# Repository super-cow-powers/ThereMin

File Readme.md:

# ThereMin()
Minimal Digital Theremin, based on a pair of NE555p timers and an STM32G0.

## Theory of Operation
The device uses a pair of 555 timers to translate hand-position to frequency, which is measured by the STM32 and then used to modify a generated sine wave.

The 555 timers operate in the usual astable mode except with the capacitor replaced with an "antenna"; this forms a capacitor between you and the metal whose value varies with the gap between you and the antenna, which then varies the frequency of the 555 output.

The STM32 measures the period of the 555's output wave, calculating the offset from the initial state (calibration is done at power-on); the offset from the calibrated value is used to calculate an amplitude coefficient and a pitch offset. The amplitude coefficient divides a full-scale sine wave which is stored in a lookup table. The pitch offset is used to increase or decrease the time between changes of output value (by adjusting a timer's reload-point), thus stretching or compacting the output wave as required - although with an apparently exponential response, which is partially corrected by the firmware.

The signal is fed into a TDA2822 amplifier in single-ended mode (SE gave better stability on veroboard) with the input amplitude controlled by a potentiometer; the amplifier feeds into either an (optional) internal speaker or headphone jack depending on a SPDT switch.

## Hardware
The hardware is designed in KiCad. If you want to build your own, you're free to use the files so long as you don't try and blame me for anything which goes wrong as a result; it'd be nice to keep my name on the board, too.

The devices are fairly cheap - about £12-15 for the basic device with no LEDs or pitch-adjust potentiometer (which haven't been written in) - I used JLC for the boards and sourced most of the parts from DigiKey.

The cases are drilled by hand, using a 13mm bit for the rear cables, a 6.5mm and 7.5mm bit for the front switch and pot, and a 6mm bit for the (four) holes on the top. There's no drilling template, just use a centre-punch in the right place for the hole's purpose and drill. 

### "Antennae"
The Antennae (capacitor plates, really) are not too critical. Mine are made from thin brass rod which will fit into the jacks; any conductor which fits the jacks will work - make it into a loop which looks like a theremin antenna aught, with one "leg" slightly shorter than the other for the non-connected end. The bigger the antenna the more sensitive the response generally speaking, although I've found that there's not much to gain with this device from a huge antenna.

## Firmware
The firmware uses device files from ST Micro and ARM CMSIS, the rest can be blamed on me. The ST HAL is not being used, because it looked like a good idea to not use it when I started...

The software is fairly simple although does make heavy use of the DMA engine and Timers - these are described in the chip reference manual and, briefly, in comments.

### Building
The firmware builds with Make and Arm GCC (I suspect ARMCC6 would work, too, but I'm not going to try it) and should build on most *nix systems - it might work on Windows under WSL or mingw, but you're on your own with that one. For anyone who doesn't want to build the firmware, the latest binary is just in the build directory.

The firmware can be flashed with your favourite flashing tool; a script for an ST-Link V2 with OpenOCD is provided, but I recommend just using STMCubeProg if you're either inexperienced or running Windows. 

-----

This was initially designed as a lab kit for the [York Engineering Society](https://github.com/EngYork).

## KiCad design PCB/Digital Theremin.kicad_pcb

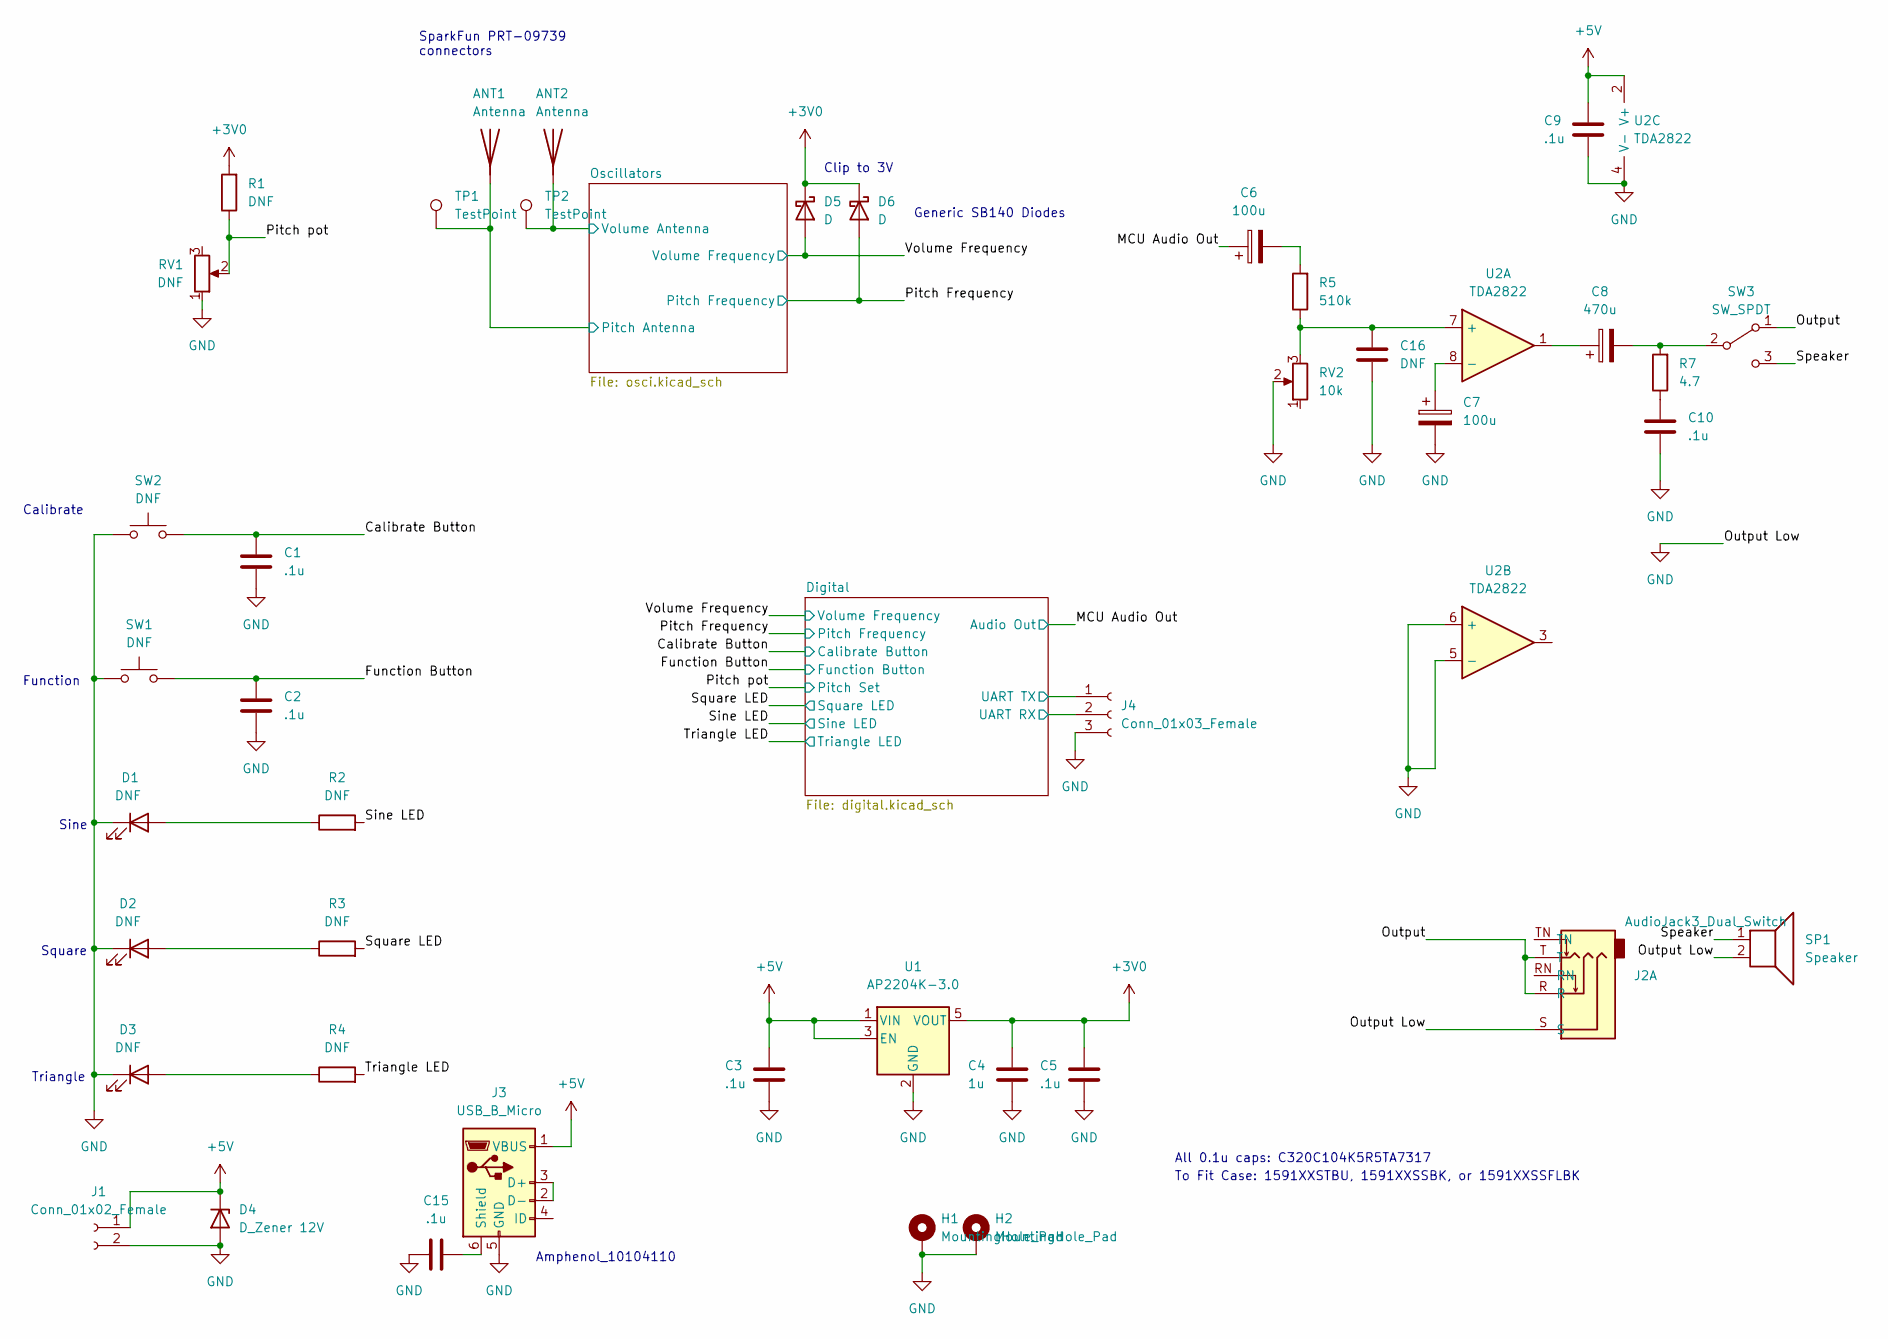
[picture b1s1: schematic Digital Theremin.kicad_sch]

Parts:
ANT1, ANT2: Antenna; MountingHole_3.2mm_M3_Pad_Via
C1, C2, C3, C5, C9, C10, C15: .1u; C_Rect_L4.0mm_W2.5mm_P2.50mm
C4: 1u; C_Rect_L4.0mm_W2.5mm_P2.50mm
C6, C7: 100u; CP_Radial_D5.0mm_P2.50mm
C8: 470u; CP_Radial_D5.0mm_P2.50mm
C16: DNF; C_Rect_L4.0mm_W2.5mm_P2.50mm
D1, D2, D3: DNF; LED_D5.0mm
D4: D_Zener 12V; D_DO-41_SOD81_P10.16mm_Horizontal
D5, D6: D; D_DO-41_SOD81_P10.16mm_Horizontal
H1, H2: MountingHole_Pad; MountingHole_3.7mm_Pad
J1: Conn_01x02_Female; PinHeader_1x02_P2.54mm_Vertical
J2: AudioJack3_Dual_Switch; Jack_3.5mm_CUI_SJ1-3525N_Horizontal
J3: USB_B_Micro; USB_Micro-B_Amphenol_10104110_Horizontal
J4: Conn_01x03_Female; PinHeader_1x03_P2.54mm_Vertical
R1, R2, R3, R4: DNF; R_Axial_DIN0207_L6.3mm_D2.5mm_P10.16mm_Horizontal
R5: 510k; R_Axial_DIN0207_L6.3mm_D2.5mm_P10.16mm_Horizontal
R7: 4.7; R_Axial_DIN0207_L6.3mm_D2.5mm_P10.16mm_Horizontal
RV1: DNF; PinHeader_1x03_P2.54mm_Vertical
RV2: 10k; PinHeader_1x03_P2.54mm_Vertical
SP1: Speaker; PinHeader_1x02_P2.54mm_Vertical
SW1, SW2: DNF; SW_PUSH_6mm
SW3: SW_SPDT; PinHeader_1x03_P2.54mm_Vertical
TP1, TP2: TestPoint; TestPoint_Loop_D2.50mm_Drill1.0mm
U1: AP2204K-3.0; SOT-23-5
U2: TDA2822; SOIC-8_3.9x4.9mm_P1.27mm

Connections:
+3V0: C4.1, C5.1, D5.1 (K), D6.1 (K), R1.2, U1.5 (VOUT); also elsewhere on the board
+5V: C3.1, C9.1, D4.1 (K), J1.1, J3.1 (VBUS), U1.1 (VIN), U1.3 (EN), U2.2 (V+); also elsewhere on the board
/Calibrate Button: C1.2, SW2.2; also elsewhere on the board
/Digital/UART RX: J4.2; also elsewhere on the board
/Digital/UART TX: J4.1; also elsewhere on the board
/Function Button: C2.2, SW1.2; also elsewhere on the board
/MCU Audio Out: C6.1; also elsewhere on the board
/Oscillators/Pitch Antenna: ANT1.1 (A), TP1.1; also elsewhere on the board
/Oscillators/Volume Antenna: ANT2.1 (A), TP2.1; also elsewhere on the board
/Output: J2.R, J2.T, SW3.1 (A)
/Pitch Frequency: D6.2 (A); also elsewhere on the board
/Pitch pot: R1.1, RV1.2; also elsewhere on the board
/Sine LED: R2.2; also elsewhere on the board
/Speaker: SP1.1, SW3.3 (C)
/Square LED: R3.2; also elsewhere on the board
/Triangle LED: R4.2; also elsewhere on the board
/Volume Frequency: D5.2 (A); also elsewhere on the board
GND: C1.1, C2.1, C3.2, C4.2, C5.2, C7.2, C9.2, C10.1, C15.2, C16.1, D1.1 (K), D2.1 (K), D3.1 (K), D4.2 (A), H1.1, H2.1, J1.2, J2.S, J3.5 (GND), J4.3, RV1.1, RV2.2, SP1.2, SW1.1, SW2.1, U1.2 (GND), U2.4 (V-), U2.5 (-), U2.6 (+); also elsewhere on the board
unnamed: C6.2, R5.2
unnamed: C7.1, U2.8 (-)
unnamed: C8.1, U2.1
unnamed: C8.2, R7.2, SW3.2 (B)
unnamed: C10.2, R7.1
unnamed: C15.1, J3.6 (Shield)
unnamed: C16.2, R5.1, RV2.3, U2.7 (+)
unnamed: D1.2 (A), R2.1
unnamed: D2.2 (A), R3.1
unnamed: D3.2 (A), R4.1
unnamed: J3.2 (D-), J3.3 (D+)

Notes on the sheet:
Generic SB140 Diodes
Square
Triangle
All 0.1u caps: C320C104K5R5TA7317
To Fit Case: 1591XXSTBU, 1591XXSSBK, or 1591XXSSFLBK
Clip to 3V
SparkFun PRT-09739 connectors
Sine
Calibrate
Function
Amphenol_10104110

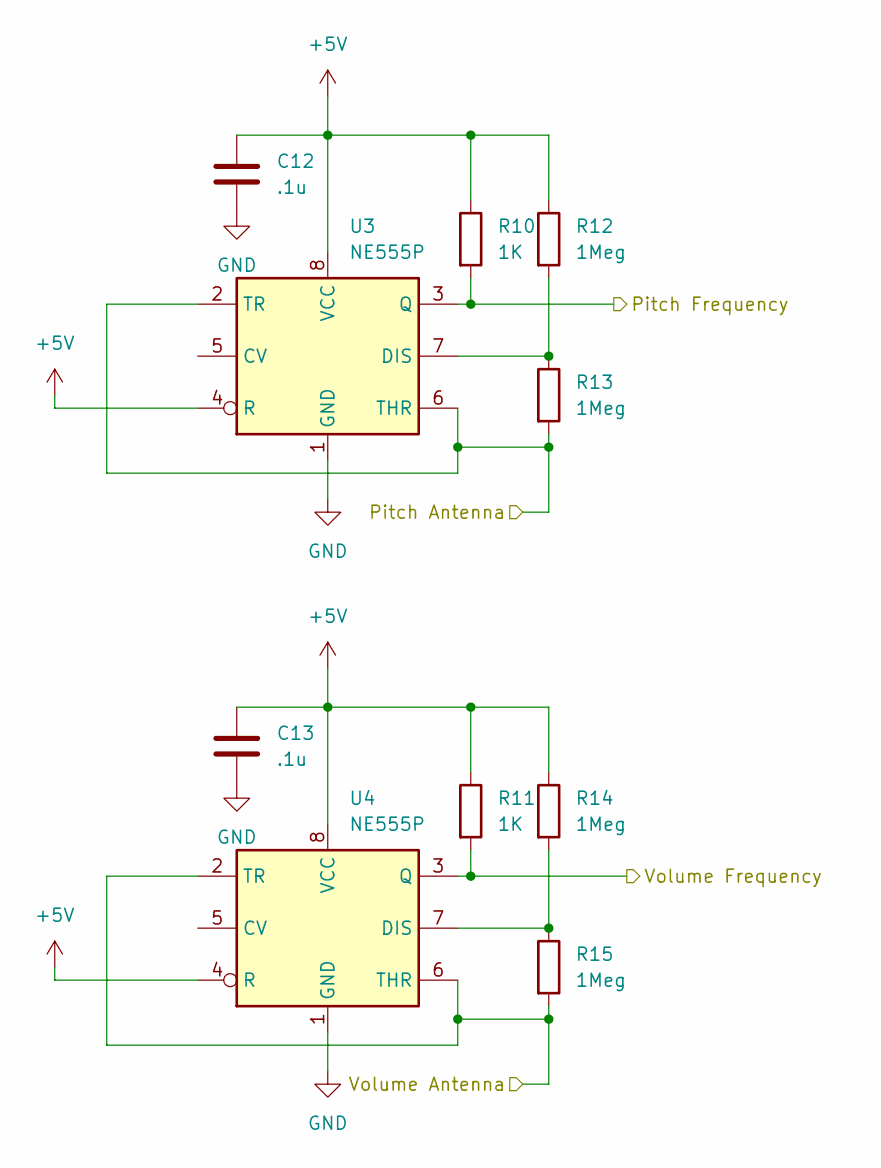
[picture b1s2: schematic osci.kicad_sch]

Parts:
C12, C13: .1u; C_Rect_L4.0mm_W2.5mm_P2.50mm
R10, R11: 1K; R_Axial_DIN0207_L6.3mm_D2.5mm_P10.16mm_Horizontal
R12, R13, R14, R15: 1Meg; R_Axial_DIN0207_L6.3mm_D2.5mm_P10.16mm_Horizontal
U3, U4: NE555P; DIP-8_W7.62mm

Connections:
+5V: C12.1, C13.1, R10.1, R11.1, R12.1, R14.1, U3.4 (R), U3.8 (VCC), U4.4 (R), U4.8 (VCC); also elsewhere on the board
/Oscillators/Pitch Antenna: R13.2, U3.2 (TR), U3.6 (THR); also elsewhere on the board
/Oscillators/Volume Antenna: R15.2, U4.2 (TR), U4.6 (THR); also elsewhere on the board
/Pitch Frequency: R10.2, U3.3 (Q); also elsewhere on the board
/Volume Frequency: R11.2, U4.3 (Q); also elsewhere on the board
GND: C12.2, C13.2, U3.1 (GND), U4.1 (GND); also elsewhere on the board
unnamed: R12.2, R13.1, U3.7 (DIS)
unnamed: R14.2, R15.1, U4.7 (DIS)

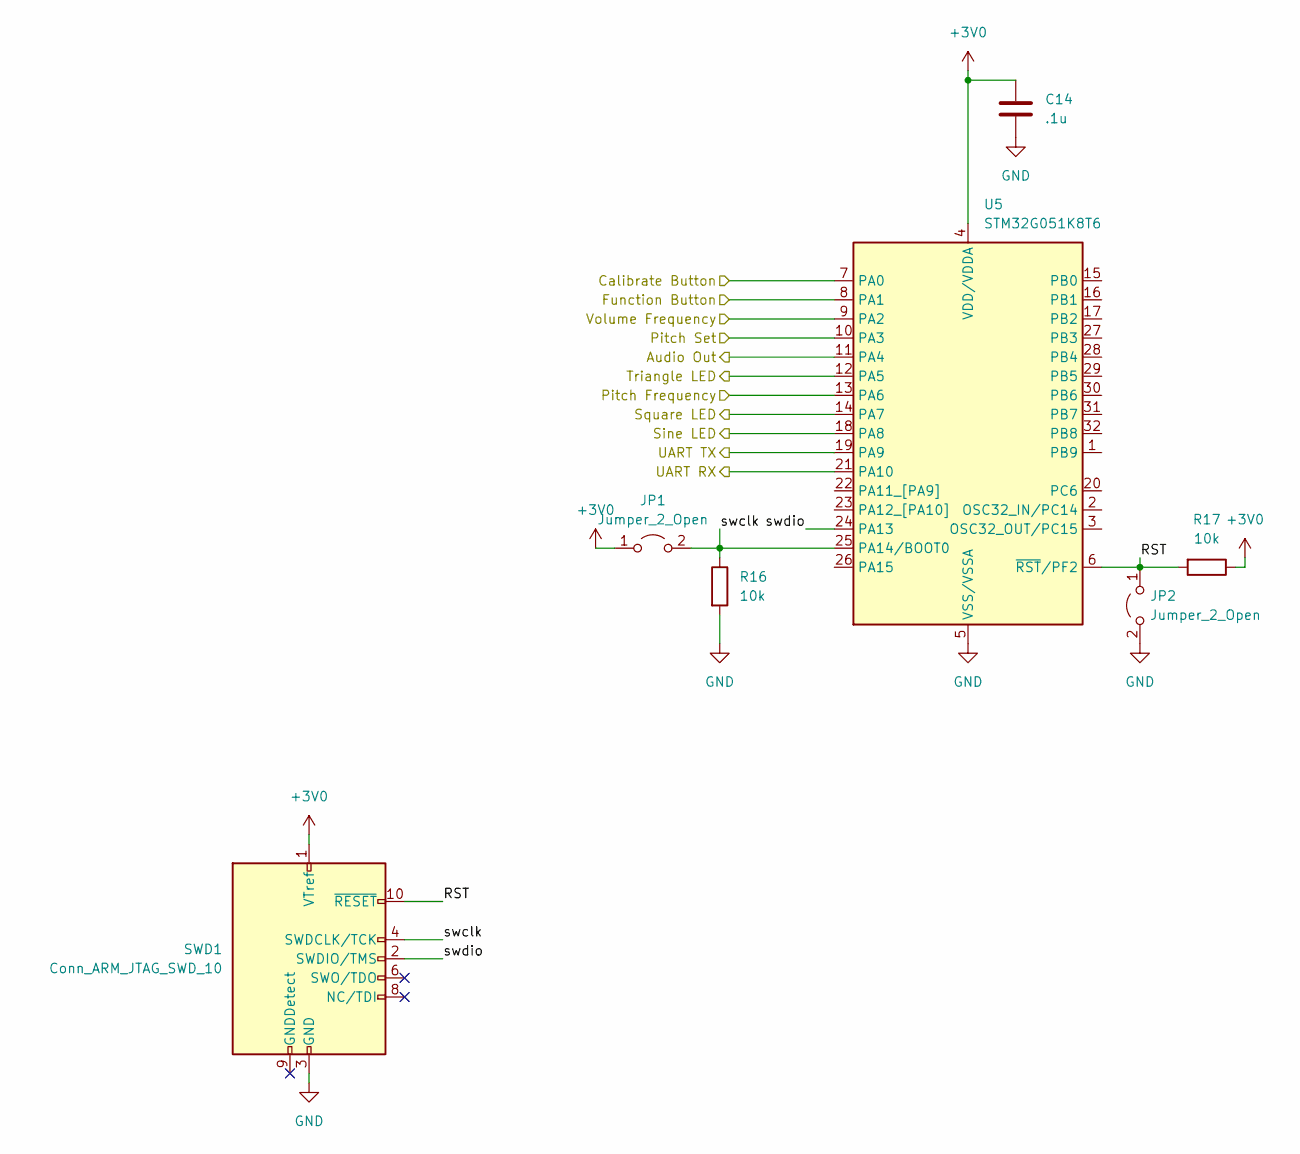
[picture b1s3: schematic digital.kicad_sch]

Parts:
C14: .1u; C_Rect_L4.0mm_W2.5mm_P2.50mm
JP1, JP2: Jumper_2_Open; SolderJumper-2_P1.3mm_Open_TrianglePad1.0x1.5mm
R16, R17: 10k; R_Axial_DIN0207_L6.3mm_D2.5mm_P10.16mm_Horizontal
SWD1: Conn_ARM_JTAG_SWD_10; PinHeader_2x05_P1.27mm_Vertical
U5: STM32G051K8T6; LQFP-32_7x7mm_P0.8mm

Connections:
+3V0: C14.2, JP1.1 (A), R17.1, SWD1.1 (VTref), U5.4 (VDD/VDDA); also elsewhere on the board
/Calibrate Button: U5.7 (PA0); also elsewhere on the board
/Digital/RST: JP2.1 (A), R17.2, SWD1.10 (~RESET), U5.6 (~RST/PF2)
/Digital/UART RX: U5.21 (PA10); also elsewhere on the board
/Digital/UART TX: U5.19 (PA9); also elsewhere on the board
/Digital/swclk: JP1.2 (B), R16.1, SWD1.4 (SWDCLK/TCK), U5.25 (PA14/BOOT0)
/Digital/swdio: SWD1.2 (SWDIO/TMS), U5.24 (PA13)
/Function Button: U5.8 (PA1); also elsewhere on the board
/MCU Audio Out: U5.11 (PA4); also elsewhere on the board
/Pitch Frequency: U5.13 (PA6); also elsewhere on the board
/Pitch pot: U5.10 (PA3); also elsewhere on the board
/Sine LED: U5.18 (PA8); also elsewhere on the board
/Square LED: U5.14 (PA7); also elsewhere on the board
/Triangle LED: U5.12 (PA5); also elsewhere on the board
/Volume Frequency: U5.9 (PA2); also elsewhere on the board
GND: C14.1, JP2.2 (B), R16.2, SWD1.3 (GND), SWD1.5 (GND), U5.5 (VSS/VSSA); also elsewhere on the board

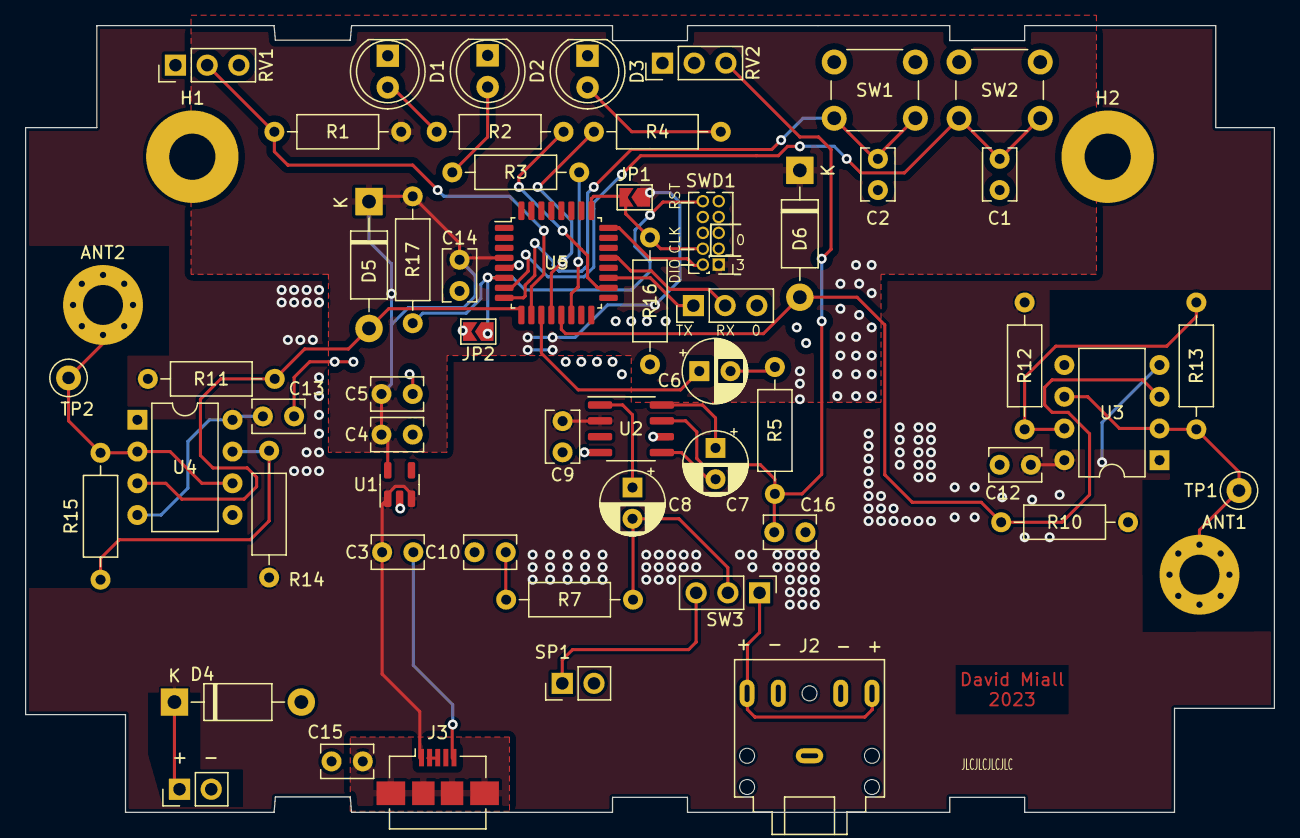
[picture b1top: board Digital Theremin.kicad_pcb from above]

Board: 2 copper layers, 100.0 x 63.0 mm, 59 parts (0 on the bottom side), 34 nets.

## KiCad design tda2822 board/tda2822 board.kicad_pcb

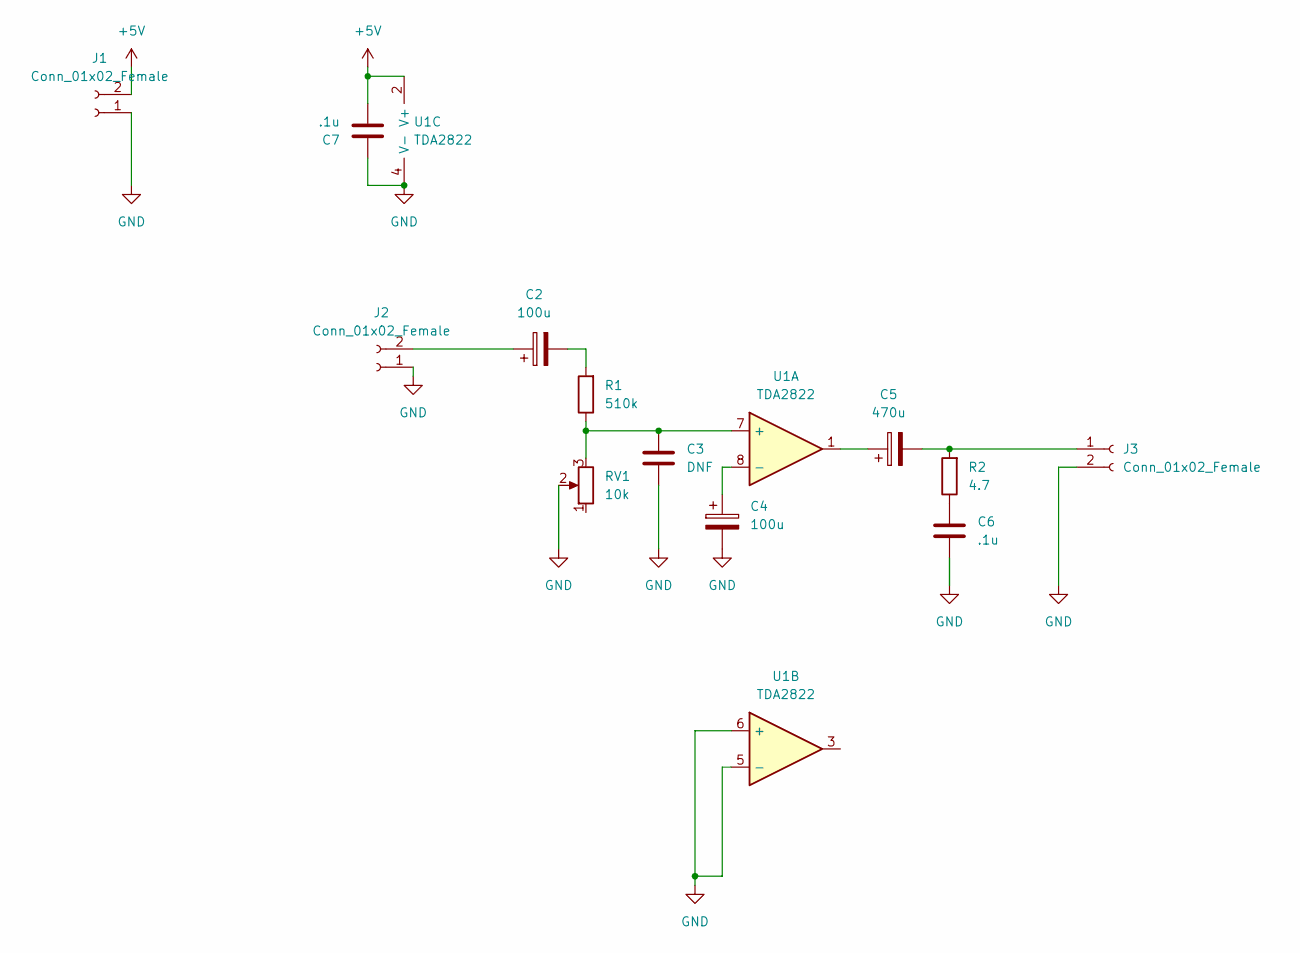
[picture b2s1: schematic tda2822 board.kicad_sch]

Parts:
C2, C4: 100u; CP_Radial_D5.0mm_P2.50mm
C3: DNF; C_Rect_L4.0mm_W2.5mm_P2.50mm
C5: 470u; CP_Radial_D5.0mm_P2.50mm
C6, C7: .1u; C_Rect_L4.0mm_W2.5mm_P2.50mm
J1, J2, J3: Conn_01x02_Female; PinHeader_1x02_P2.54mm_Vertical
R1: 510k; R_Axial_DIN0207_L6.3mm_D2.5mm_P10.16mm_Horizontal
R2: 4.7; R_Axial_DIN0207_L6.3mm_D2.5mm_P10.16mm_Horizontal
RV1: 10k; PinHeader_1x03_P2.54mm_Vertical
U1: TDA2822; DIP-8_W7.62mm

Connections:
+5V: C7.1, J1.2, U1.2 (V+)
GND: C3.1, C4.2, C6.1, C7.2, J1.1, J2.1, J3.2, RV1.2, U1.4 (V-), U1.5 (-), U1.6 (+)
unnamed: C2.1, J2.2
unnamed: C2.2, R1.2
unnamed: C3.2, R1.1, RV1.3, U1.7 (+)
unnamed: C4.1, U1.8 (-)
unnamed: C5.1, U1.1
unnamed: C5.2, J3.1, R2.2
unnamed: C6.2, R2.1

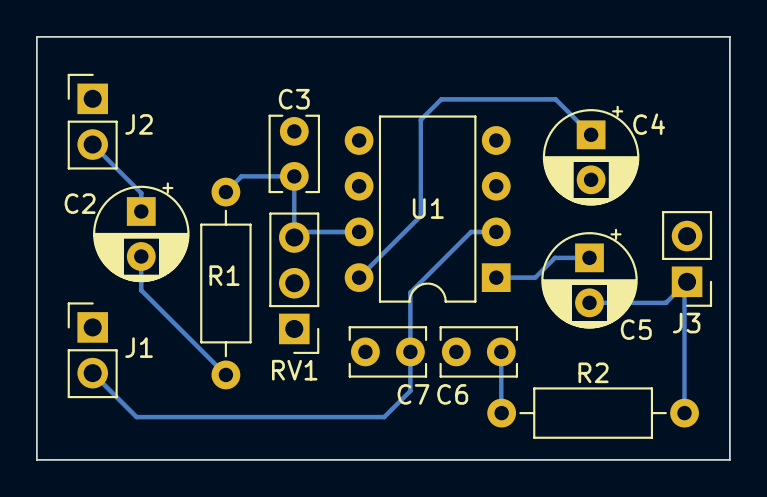
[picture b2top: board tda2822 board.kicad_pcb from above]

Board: 2 copper layers, 38.5 x 23.5 mm, 13 parts (0 on the bottom side), 9 nets.

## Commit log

2023-05-16 init
2023-05-16 Oscillators
2023-05-16 Readme
2023-05-16 Schematic
2023-05-22 Schematics
2023-05-23 Software
2023-05-23 DAC Output a Sine Wave. Re-add Bridge amp
2023-05-24 Cleanup
2023-05-24 Software. Add filter cap
2023-05-25 Measure frequency from timers
2023-05-26 Working pitch. Revert to Single Ended amplifier
2023-05-26 Volume and pitch
2023-05-27 Single ended layout
2023-05-28 Antenna mounts
2023-05-29 Flip amp board
2023-06-29 Add G0 files
2023-07-04 Working Software for board
2023-07-04 Remove g0 hal
2023-07-04 Add Binary
2023-07-04 Add elf
2023-07-04 Remove temps
2023-07-04 Image
2023-07-04 Spelling
2023-07-04 housekeeping
2023-07-04 Set DNF
2023-07-04 adjust pitch scaling
2023-07-13 Add how-to
